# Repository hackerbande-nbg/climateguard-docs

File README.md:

# General Overview

https://miro.com/app/board/uXjVKgZp_hM=/

# Infra Documentation

[infra](infra.md)

# Quantum telemetry docs

[quantum-telemetry](quantum-telemetry.md)

# Hardware
[Hardware](./hardware/hardware.md)
[Inventory](./hardware/inventory.md)

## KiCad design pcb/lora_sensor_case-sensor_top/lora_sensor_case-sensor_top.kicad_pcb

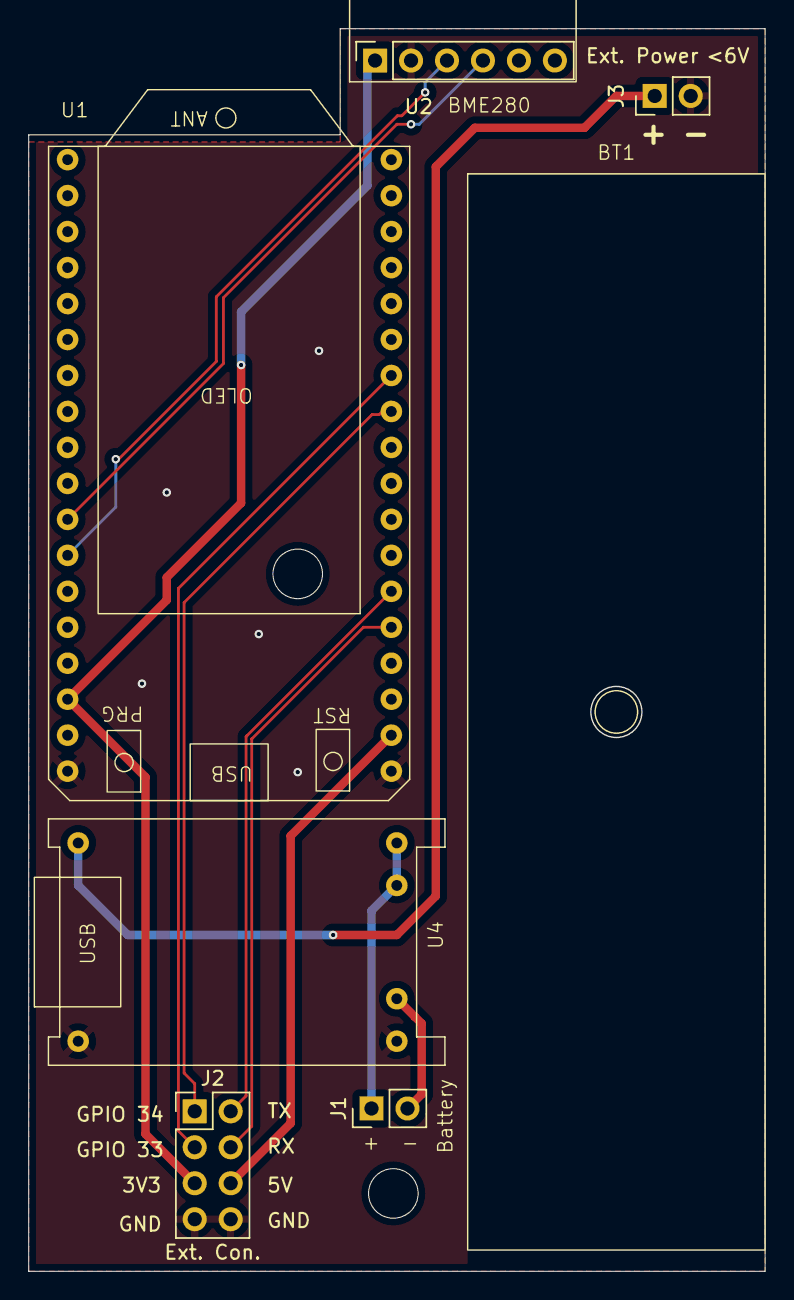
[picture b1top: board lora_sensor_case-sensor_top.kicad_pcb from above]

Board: 2 copper layers, 52.0 x 87.7 mm, 7 parts (0 on the bottom side), 12 nets.

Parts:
BT1: Battery_Cell; Batteriehalter 18650
J1: Battery Connector; PinHeader_1x02_P2.54mm_Vertical
J2: Ext. Con.; PinHeader_2x04_P2.54mm_Vertical
J3: External Power Supply (5V); PinHeader_1x02_P2.54mm_Vertical
U1: Heltec_HTIT-WB32; Heltec Lora
U2: BME280
U4: TP4056

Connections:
+3V3: J2.5, U1.21 (3.3), U2.1 (VCC)
+5V: J2.6, U1.2 (5V)
/GPIO_33: J2.3, U1.12 (33)
/GPIO_34: J2.1, U1.11 (34)
/SCL: U1.25 (42), U2.3 (SCL)
/SDA: U1.26 (41), U2.4 (SDA)
/UART_RX: J2.4, U1.5 (RX)
/UART_TX: J2.2, U1.6 (TX)
GND: J2.7, J2.8, J3.2, U1.1 (GND), U1.19 (GND), U2.2 (GND), U4.2 (In-), U4.6 (Out-)
GNDA: J1.2, U4.5 (Bat-)
VCC: J1.1, U4.3 (Out+), U4.4 (Bat+)
VDD: J3.1, U4.1 (In+)

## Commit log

2025-03-16 feat: first commit
2025-03-16 bug: remove broken table
2025-03-16 feat: add miro link
2025-03-16 Update infra.md
    add api url
2025-03-16 add nginx to infra.md
2025-03-16 add server information infra.md
2025-03-18 feat: add quantum env varriables
2025-03-20 feat: add quantum-telemetry datamodel docs
2025-03-20 fix: naming
2025-04-30 feat: Copy Hardware Docs from mess repo
2025-10-21 feat: init commit
2025-10-21 feat: add ttn analysis
2025-10-21 feat: add additional ionfo and json
2025-10-21 feat: add link to sample
2025-10-21 feat: add timing diagram
2025-10-21 bug: remove json
2025-10-21 Ttn fields (#1)
    * feat: add ttn analysis
    * feat: add additional ionfo and json
    * feat: add link to sample
    * feat: add timing diagram
    * bug: remove json
2025-10-21 featgst
2025-10-22 feat: add db size
2025-10-29 feat: add first draft of experiment
2025-10-29 feat: battery longevity in review
2025-11-24 Add new persona for Tobias Müller and update Lisa Meier
2025-11-24 Refine personas for clarity and consistency
    Corrected formatting and improved wording in personas for clarity.
2025-11-24 Add persona for Dr. Felix Hartmann, urban planner
2025-11-24 Revise personas and add Klaus Weber's profile
    Updated sections on motivation and needs for personas, replacing 'Aufgaben & Ziele' with 'Motivation & Bedürfnisse'. Added a new persona, Klaus Weber, detailing his background and interests related t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
2025-11-24 Update location for Klaus Weber persona
2025-12-03 Add image to Table Overview in info.md
    Added an image to the database info documentation.
